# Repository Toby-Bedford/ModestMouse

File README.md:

# ModestMouse

Firmware for a dsPIC30F4011 based, maze solving, robotics platform.
<br>
<banner>ooh i can edit</banner>
</br>

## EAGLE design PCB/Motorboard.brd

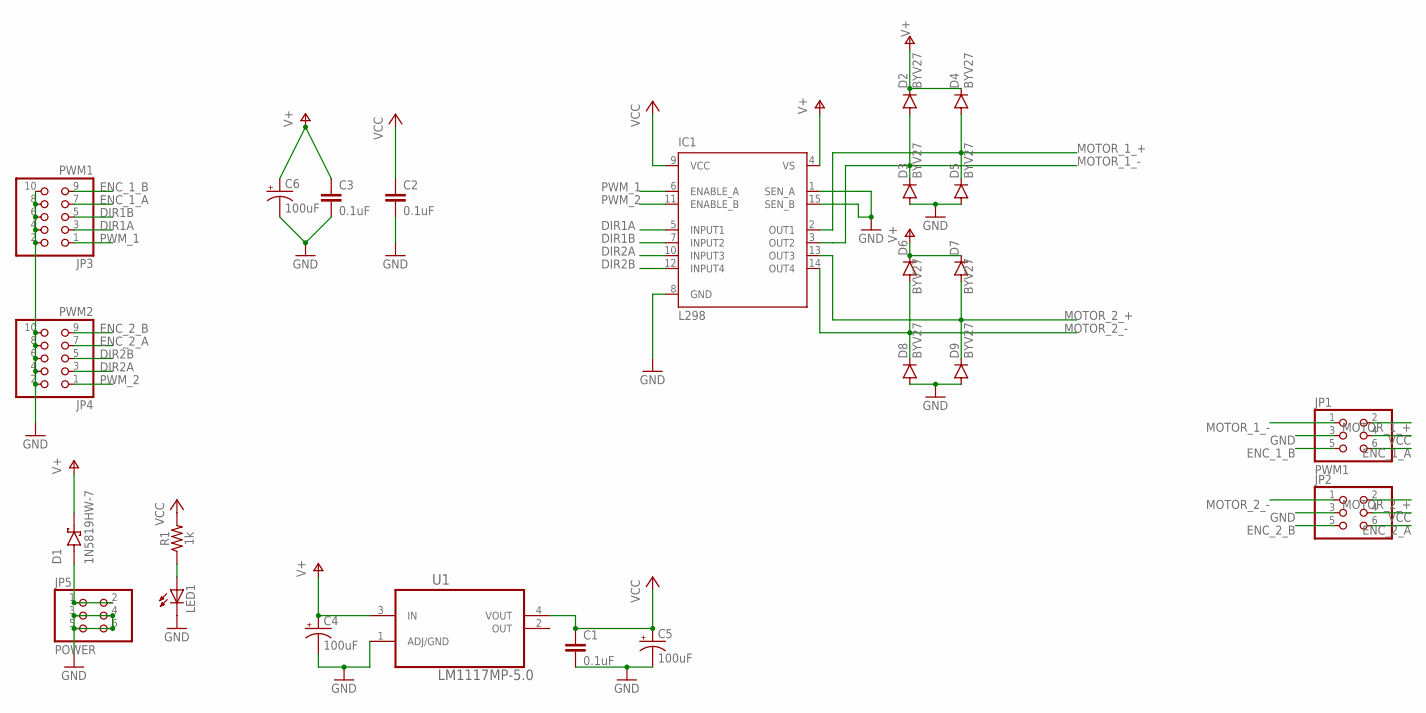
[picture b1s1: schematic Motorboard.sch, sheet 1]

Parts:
C1, C2, C3: 0.1uF; 0603
C4, C5, C6: 100uF; CPOL-RADIAL-2.5MM-6.5MM
D1: 1N5819HW-7; SOD3715X145N
D2, D3, D4, D5, D6, D7, D8, D9: BYV27; SOD57-10
IC1: L298; MULTIWATT-15
JP1: PWM1; 2X03
JP2: PINHD-2X3; 2X03
JP3: PWM1; 2X05
JP4: PWM2; 2X05
JP5: POWER; 2X03
LED1: LED3MM
R1: 1k; 0603
U1: LM1117MP-5.0; SOT230P696X180-4N

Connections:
+5V: C1.1, C2.1, C5.1 (+), IC1.9 (VCC), R1.2, U1.4 (VOUT)
DIR1A: IC1.5 (INPUT1), JP3.3
DIR1B: IC1.7 (INPUT2), JP3.5
DIR2A: IC1.10 (INPUT3), JP4.3
DIR2B: IC1.12 (INPUT4), JP4.5
ENC_1_A: JP1.6, JP3.7
ENC_1_B: JP1.5, JP3.9
ENC_2_A: JP2.6, JP4.7
ENC_2_B: JP2.5, JP4.9
GND: C1.2, C2.2, C3.2, C4.2 (-), C5.2 (-), C6.2 (-), D3.A, D5.A, D8.A, D9.A, IC1.1 (SEN_A), IC1.8 (GND), IC1.15 (SEN_B), JP1.3, JP2.3, JP3.2, JP3.4, JP3.6, JP3.8, JP3.10, JP4.2, JP4.4, JP4.6, JP4.8, JP4.10, JP5.3, JP5.4, JP5.5, JP5.6, LED1.K (C), U1.1 (ADJ/GND)
MOTOR_1_+: D4.A, D5.C, IC1.2 (OUT1), JP1.2
MOTOR_1_-: D2.A, D3.C, IC1.3 (OUT2), JP1.1
MOTOR_2_+: D7.A, D9.C, IC1.13 (OUT3), JP2.2
MOTOR_2_-: D6.A, D8.C, IC1.14 (OUT4), JP2.1
unnamed: LED1.A, R1.1
unnamed: D1.A, JP5.1, JP5.2
PWM_1: IC1.6 (ENABLE_A), JP3.1
PWM_2: IC1.11 (ENABLE_B), JP4.1
V+: C3.1, C4.1 (+), C6.1 (+), D1.C (K), D2.C, D4.C, D6.C, D7.C, IC1.4 (VS), U1.3 (IN)
VCC: JP1.4, JP2.4

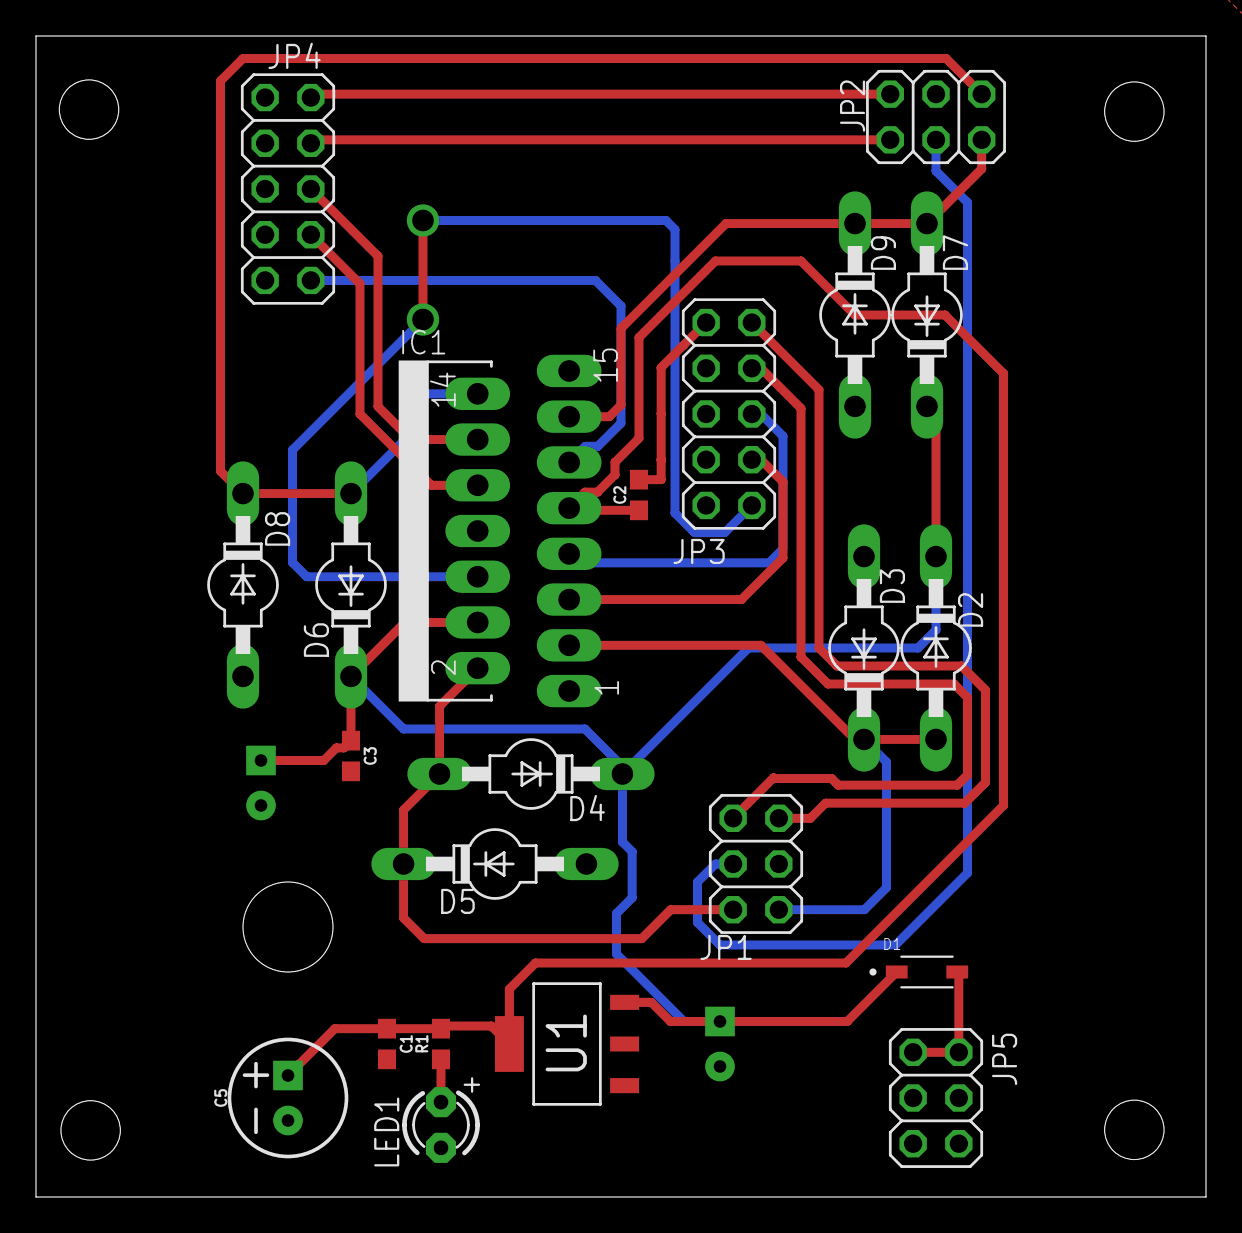
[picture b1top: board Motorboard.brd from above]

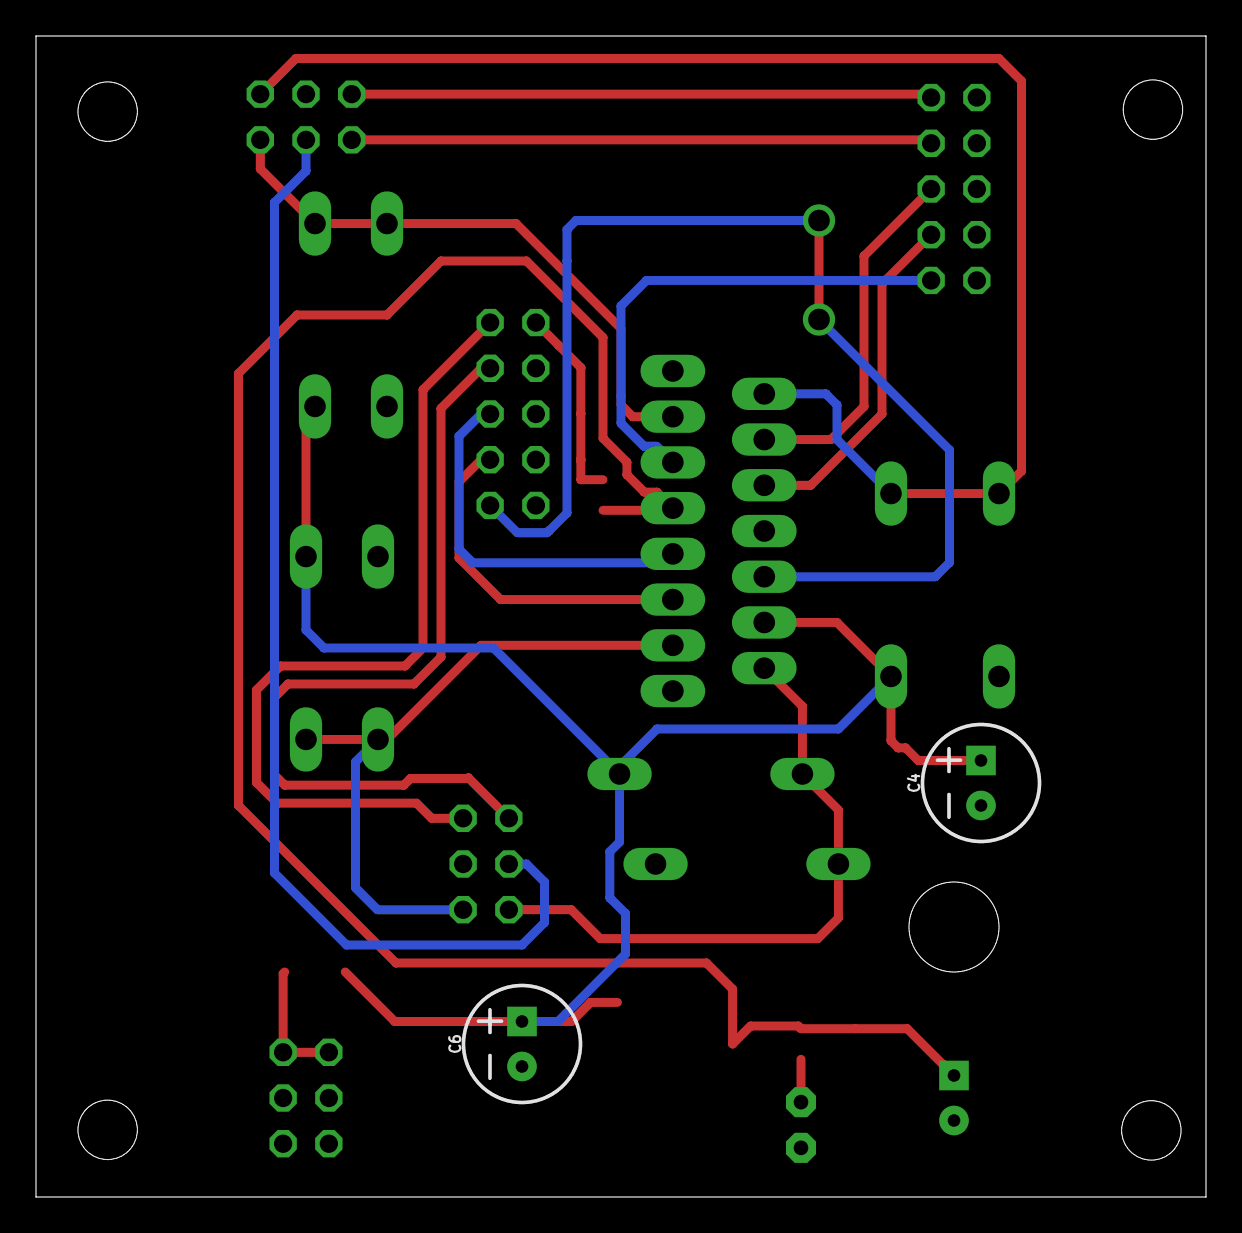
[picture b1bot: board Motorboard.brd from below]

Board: 2 copper layers, 65.0 x 64.5 mm, 24 parts (2 on the bottom side), 20 nets.

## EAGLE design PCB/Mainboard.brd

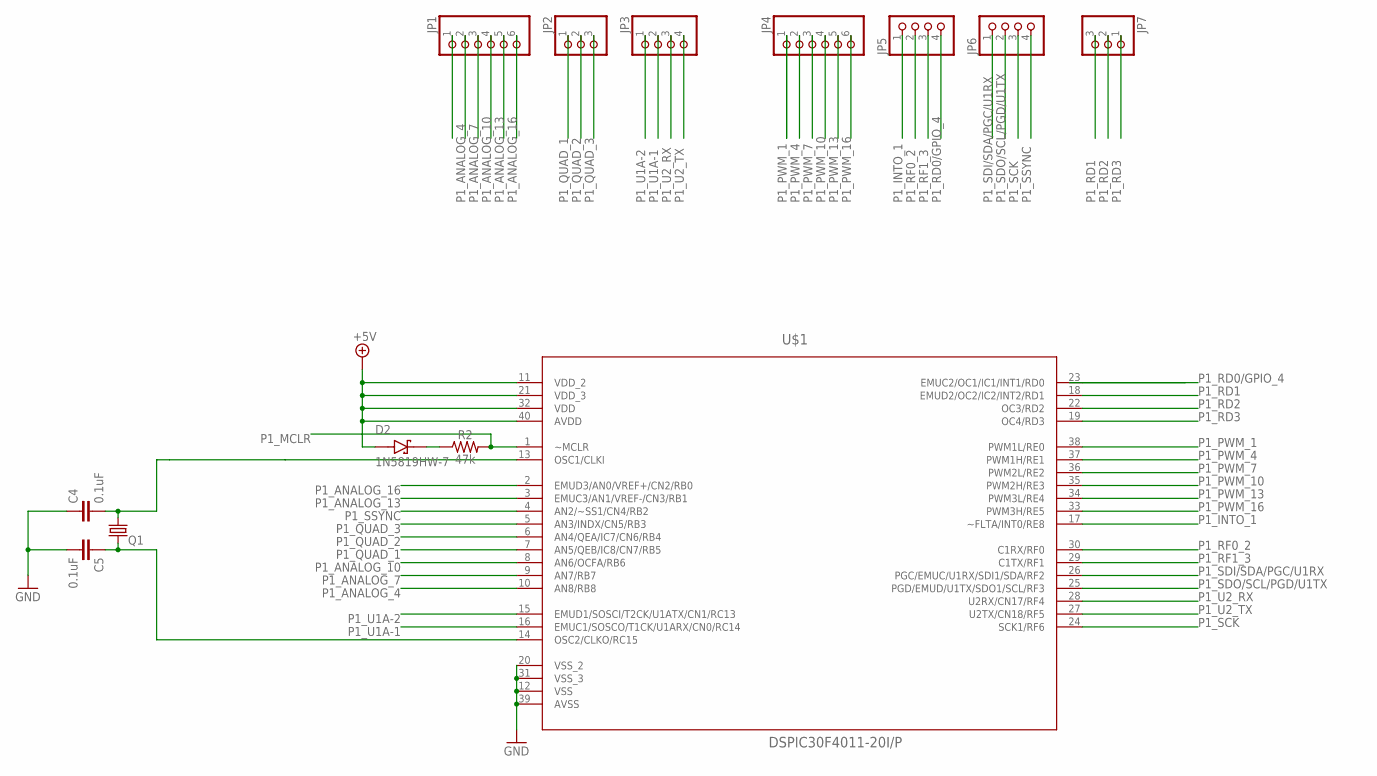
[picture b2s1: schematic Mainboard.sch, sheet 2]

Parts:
C4, C5: 0.1uF; 0603
D2: 1N5819HW-7; SOD3715X145N
JP1, JP4: PINHD-1X6; 1X06
JP2, JP7: PINHD-1X3; 1X03
JP3, JP5, JP6: PINHD-1X4; 1X04
Q1: CRYSTALHC49UP; HC49UP
R2: 47k; 0603
U$1: DSPIC30F4011-20I/P; DIP254P1524X635-40

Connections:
+5V: D2.A, U$1.11 (VDD_2), U$1.21 (VDD_3), U$1.32 (VDD), U$1.40 (AVDD); also elsewhere on the board
GND: C4.1, C5.2, U$1.12 (VSS), U$1.20 (VSS_2), U$1.31 (VSS_3), U$1.39 (AVSS); also elsewhere on the board
unnamed: C4.2, Q1.2, U$1.13 (OSC1/CLKI)
unnamed: D2.C (K), R2.1
unnamed: C5.1, Q1.1, U$1.14 (OSC2/CLKO/RC15)
P1_ANALOG_4: JP1.2, U$1.10 (AN8/RB8)
P1_ANALOG_7: JP1.3, U$1.9 (AN7/RB7)
P1_ANALOG_10: JP1.4, U$1.8 (AN6/OCFA/RB6)
P1_ANALOG_13: JP1.5, U$1.3 (EMUC3/AN1/VREF-/CN3/RB1)
P1_ANALOG_16: JP1.6, U$1.2 (EMUD3/AN0/VREF+/CN2/RB0)
P1_INTO_1: JP5.1, U$1.17 (~FLTA/INT0/RE8)
P1_MCLR: R2.2, U$1.1 (~MCLR)
P1_PWM_1: JP4.1, U$1.38 (PWM1L/RE0)
P1_PWM_4: JP4.2, U$1.37 (PWM1H/RE1)
P1_PWM_7: JP4.3, U$1.36 (PWM2L/RE2)
P1_PWM_10: JP4.4, U$1.35 (PWM2H/RE3)
P1_PWM_13: JP4.5, U$1.34 (PWM3L/RE4)
P1_PWM_16: JP4.6, U$1.33 (PWM3H/RE5)
P1_QUAD_1: JP2.1, U$1.7 (AN5/QEB/IC8/CN7/RB5)
P1_QUAD_2: JP2.2, U$1.6 (AN4/QEA/IC7/CN6/RB4)
P1_QUAD_3: JP2.3, U$1.5 (AN3/INDX/CN5/RB3)
P1_RD0/GPIO_4: JP5.4, U$1.23 (EMUC2/OC1/IC1/INT1/RD0)
P1_RD1: JP7.3, U$1.18 (EMUD2/OC2/IC2/INT2/RD1)
P1_RD2: JP7.2, U$1.22 (OC3/RD2)
P1_RD3: JP7.1, U$1.19 (OC4/RD3)
P1_RF0_2: JP5.2, U$1.30 (C1RX/RF0)
P1_RF1_3: JP5.3, U$1.29 (C1TX/RF1)
P1_SCK: JP6.3, U$1.24 (SCK1/RF6)
P1_SDI/SDA/PGC/U1RX: JP6.1, U$1.26 (PGC/EMUC/U1RX/SDI1/SDA/RF2)
P1_SDO/SCL/PGD/U1TX: JP6.2, U$1.25 (PGD/EMUD/U1TX/SDO1/SCL/RF3)
P1_SSYNC: JP6.4, U$1.4 (AN2/~SS1/CN4/RB2)
P1_U1A-1: JP3.2, U$1.16 (EMUC1/SOSCO/T1CK/U1ARX/CN0/RC14)
P1_U1A-2: JP3.1, U$1.15 (EMUD1/SOSCI/T2CK/U1ATX/CN1/RC13)
P1_U2_RX: JP3.3, U$1.28 (U2RX/CN17/RF4)
P1_U2_TX: JP3.4, U$1.27 (U2TX/CN18/RF5)

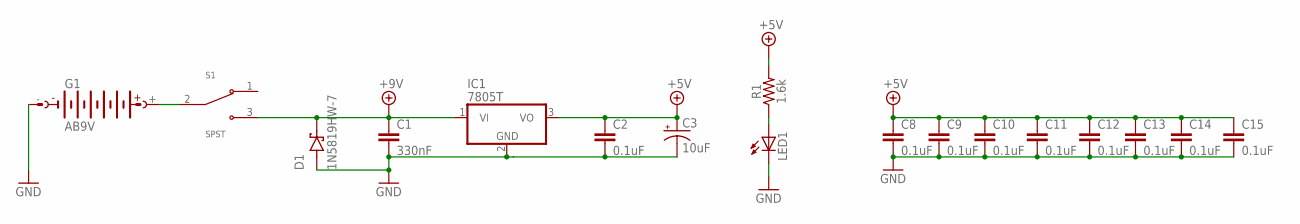
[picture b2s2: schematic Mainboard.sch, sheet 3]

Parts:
C1: 330nF; 0603
C2, C8, C9, C10, C11, C12, C13, C14, C15: 0.1uF; 0603
C3: 10uF; CPOL-RADIAL-2.5MM-5MM
D1: 1N5819HW-7; SOD3715X145N
G1: AB9V
IC1: 7805T; TO220H
LED1: LED3MM
R1: 1.6k; 0603
S1: SPST

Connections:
+5V: C2.1, C3.1 (+), C8.1, C9.1, C10.1, C11.1, C12.1, C13.1, C14.1, C15.1, IC1.3 (VO), R1.2; also elsewhere on the board
+9V: C1.1, D1.C (K), IC1.1 (VI), S1.3
GND: C1.2, C2.2, C3.2 (-), C8.2, C9.2, C10.2, C11.2, C12.2, C13.2, C14.2, C15.2, D1.A, G1.-, IC1.2 (GND), LED1.K (C); also elsewhere on the board
unnamed: G1.+, S1.2
unnamed: LED1.A, R1.1

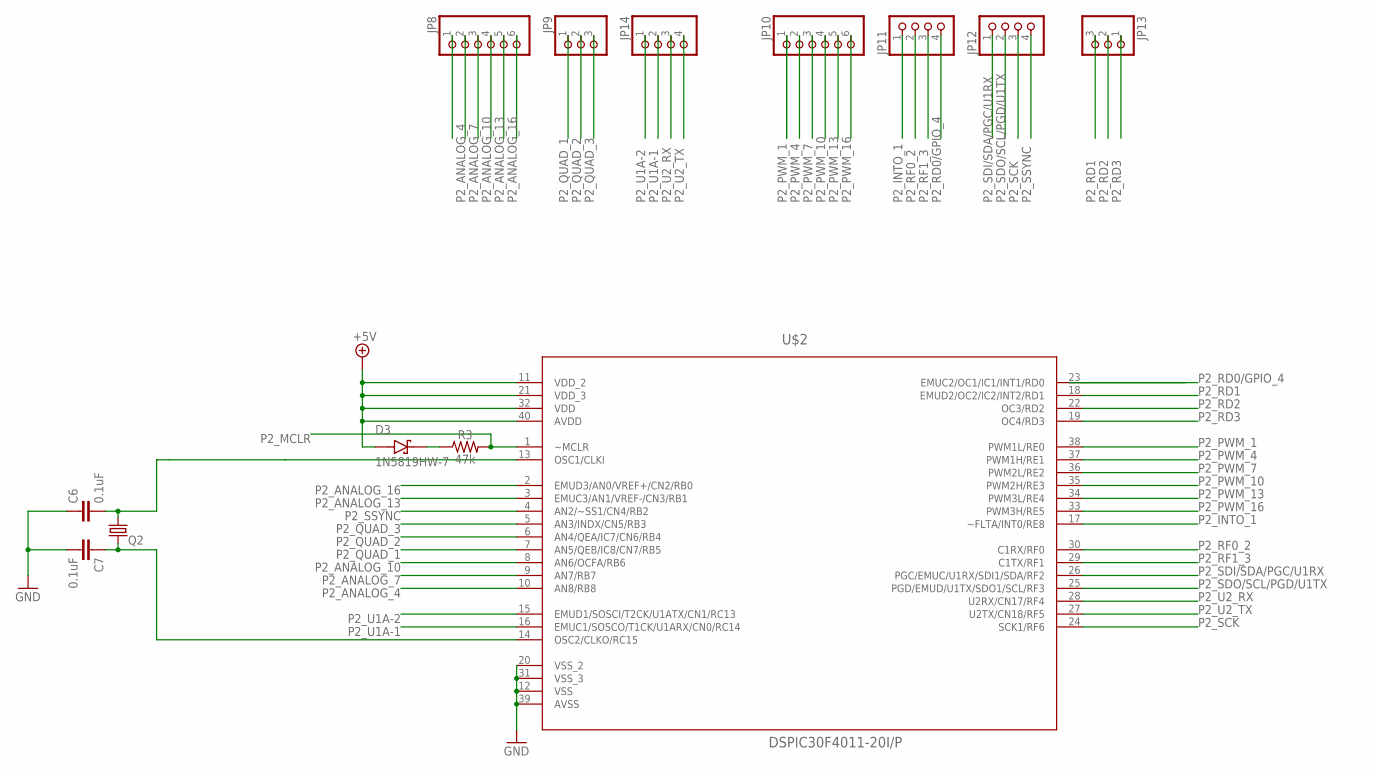
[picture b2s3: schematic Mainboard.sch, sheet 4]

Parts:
C6, C7: 0.1uF; 0603
D3: 1N5819HW-7; SOD3715X145N
JP8, JP10: PINHD-1X6; 1X06
JP9, JP13: PINHD-1X3; 1X03
JP11, JP12, JP14: PINHD-1X4; 1X04
Q2: CRYSTALHC49UP; HC49UP
R3: 47k; 0603
U$2: DSPIC30F4011-20I/P; DIP254P1524X635-40

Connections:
+5V: D3.A, U$2.11 (VDD_2), U$2.21 (VDD_3), U$2.32 (VDD), U$2.40 (AVDD); also elsewhere on the board
GND: C6.1, C7.2, U$2.12 (VSS), U$2.20 (VSS_2), U$2.31 (VSS_3), U$2.39 (AVSS); also elsewhere on the board
unnamed: D3.C (K), R3.1
unnamed: C6.2, Q2.2, U$2.13 (OSC1/CLKI)
unnamed: C7.1, Q2.1, U$2.14 (OSC2/CLKO/RC15)
P2_ANALOG_4: JP8.2, U$2.10 (AN8/RB8)
P2_ANALOG_7: JP8.3, U$2.9 (AN7/RB7)
P2_ANALOG_10: JP8.4, U$2.8 (AN6/OCFA/RB6)
P2_ANALOG_13: JP8.5, U$2.3 (EMUC3/AN1/VREF-/CN3/RB1)
P2_ANALOG_16: JP8.6, U$2.2 (EMUD3/AN0/VREF+/CN2/RB0)
P2_INTO_1: JP11.1, U$2.17 (~FLTA/INT0/RE8)
P2_MCLR: R3.2, U$2.1 (~MCLR)
P2_PWM_1: JP10.1, U$2.38 (PWM1L/RE0)
P2_PWM_4: JP10.2, U$2.37 (PWM1H/RE1)
P2_PWM_7: JP10.3, U$2.36 (PWM2L/RE2)
P2_PWM_10: JP10.4, U$2.35 (PWM2H/RE3)
P2_PWM_13: JP10.5, U$2.34 (PWM3L/RE4)
P2_PWM_16: JP10.6, U$2.33 (PWM3H/RE5)
P2_QUAD_1: JP9.1, U$2.7 (AN5/QEB/IC8/CN7/RB5)
P2_QUAD_2: JP9.2, U$2.6 (AN4/QEA/IC7/CN6/RB4)
P2_QUAD_3: JP9.3, U$2.5 (AN3/INDX/CN5/RB3)
P2_RD0/GPIO_4: JP11.4, U$2.23 (EMUC2/OC1/IC1/INT1/RD0)
P2_RD1: JP13.3, U$2.18 (EMUD2/OC2/IC2/INT2/RD1)
P2_RD2: JP13.2, U$2.22 (OC3/RD2)
P2_RD3: JP13.1, U$2.19 (OC4/RD3)
P2_RF0_2: JP11.2, U$2.30 (C1RX/RF0)
P2_RF1_3: JP11.3, U$2.29 (C1TX/RF1)
P2_SCK: JP12.3, U$2.24 (SCK1/RF6)
P2_SDI/SDA/PGC/U1RX: JP12.1, U$2.26 (PGC/EMUC/U1RX/SDI1/SDA/RF2)
P2_SDO/SCL/PGD/U1TX: JP12.2, U$2.25 (PGD/EMUD/U1TX/SDO1/SCL/RF3)
P2_SSYNC: JP12.4, U$2.4 (AN2/~SS1/CN4/RB2)
P2_U1A-1: JP14.2, U$2.16 (EMUC1/SOSCO/T1CK/U1ARX/CN0/RC14)
P2_U1A-2: JP14.1, U$2.15 (EMUD1/SOSCI/T2CK/U1ATX/CN1/RC13)
P2_U2_RX: JP14.3, U$2.28 (U2RX/CN17/RF4)
P2_U2_TX: JP14.4, U$2.27 (U2TX/CN18/RF5)

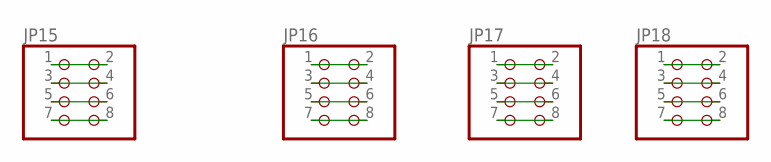
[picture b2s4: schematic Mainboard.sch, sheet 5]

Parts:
JP15, JP16, JP17, JP18: PINHD-2X4; 2X04

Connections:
unnamed: JP15.1, JP15.2
unnamed: JP15.3, JP15.4
unnamed: JP15.5, JP15.6
unnamed: JP15.7, JP15.8
unnamed: JP16.1, JP16.2
unnamed: JP16.3, JP16.4
unnamed: JP16.5, JP16.6
unnamed: JP16.7, JP16.8
unnamed: JP17.1, JP17.2
unnamed: JP17.3, JP17.4
unnamed: JP17.5, JP17.6
unnamed: JP17.7, JP17.8
unnamed: JP18.1, JP18.2
unnamed: JP18.3, JP18.4
unnamed: JP18.5, JP18.6
unnamed: JP18.7, JP18.8

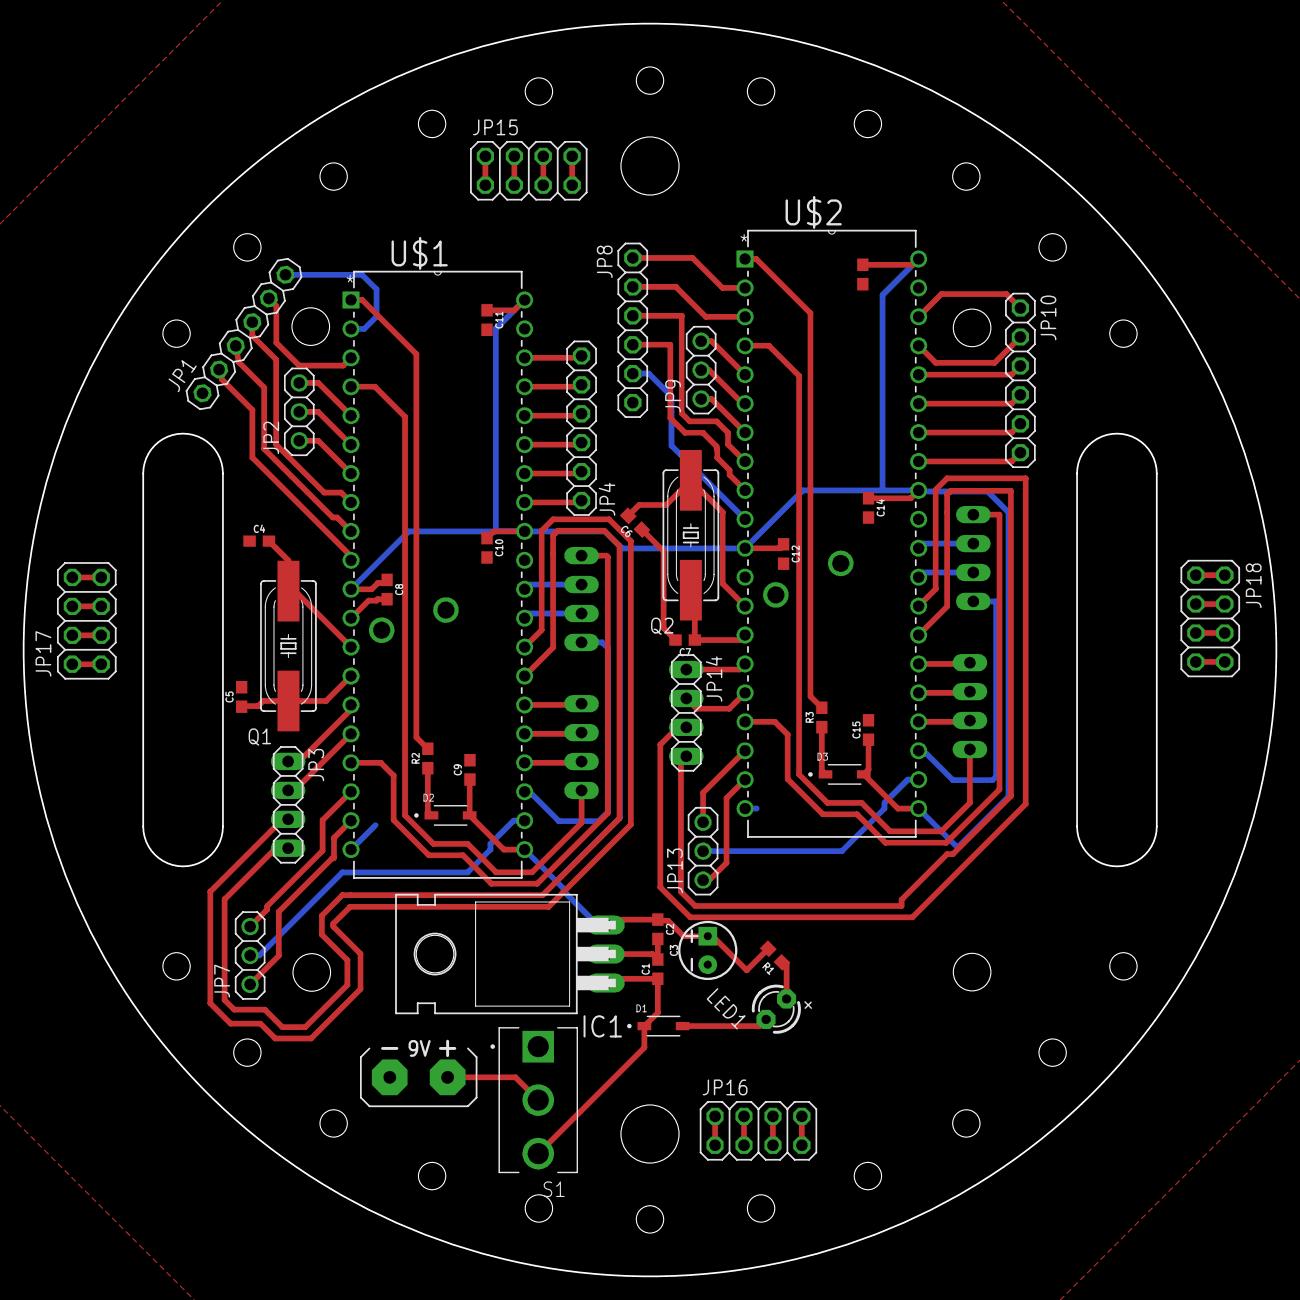
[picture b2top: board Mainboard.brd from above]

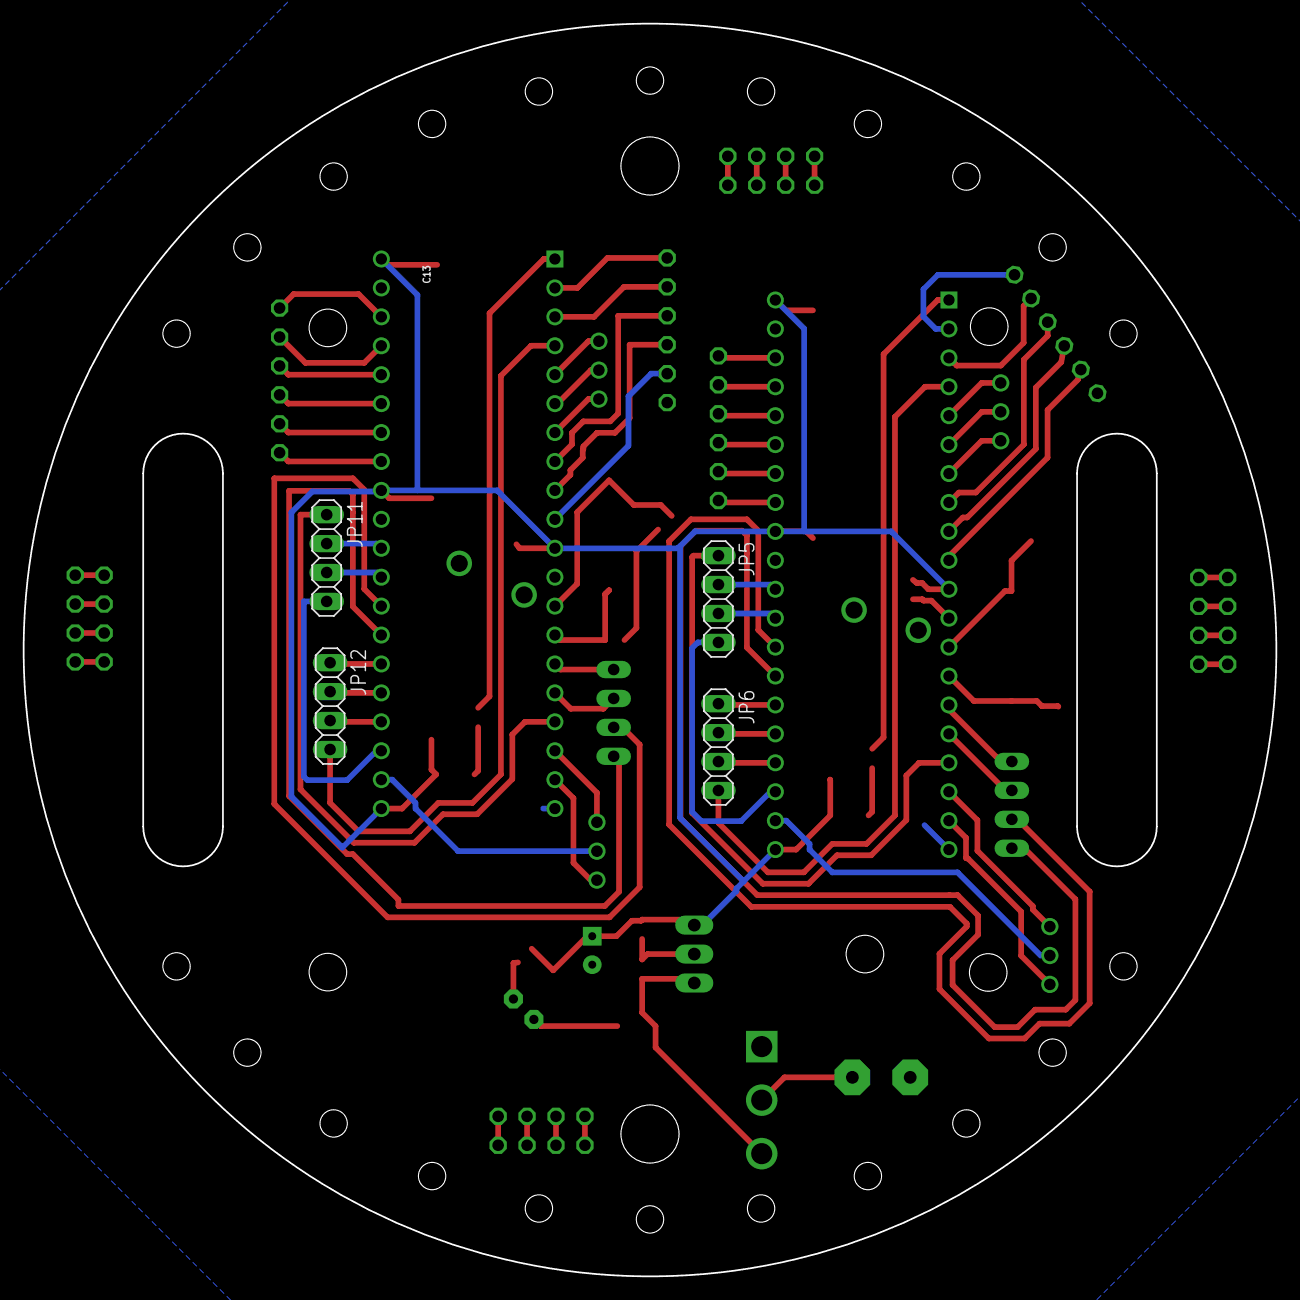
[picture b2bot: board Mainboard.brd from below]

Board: 2 copper layers, 110.0 x 110.0 mm, 47 parts (4 on the bottom side), 87 nets.

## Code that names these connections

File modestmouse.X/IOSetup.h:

/* 
 * File:   IOSetup.h
 * Author: harry
 *
 * Created on 11 January 2022, 20:32
 */

#ifndef IOSETUP_H
#define	IOSETUP_H

#include "p30F4011.h"


#ifdef	__cplusplus
extern "C" {
#endif

//Defining S3
#define S3PORT PORTDbits.RD2
#define S3TRIS TRISDbits.TRISD2
#define S3LAT LATDbits.LATD2
    
//Defining LED2
#define LED2PORT PORTDbits.RD1
#define LED2TRIS TRISDbits.TRISD1
#define LED2LAT LATDbits.LATD1
    
//Defining LED3
#define LED3PORT PORTDbits.RD3
#define LED3TRIS TRISDbits.TRISD3
#define LED3LAT LATDbits.LATD3
    
//Defining LED4
#define LED4PORT PORTEbits.RE0
#define LED4TRIS TRISEbits.TRISE0
#define LED4LAT LATEbits.LATE0
    
// 23/03/2022
// Switched motors pins to from RB7 --> RB5 & RB8 --> RB6
#define PIN37PORT PORTBbits.RB5
#define PIN37TRIS TRISBbits.TRISB5
#define PIN37LAT LATBbits.LATB5
    
#define PIN36PORT PORTBbits.RB6
#define PIN36TRIS TRISBbits.TRISB6
#define PIN36LAT LATBbits.LATB6

// Added setup pins for ultrasonic sensor.
#define echoPin PORTBbits.RB7
#define ECHO_tris TRISBbits.TRISB7
    
#define TRIG_tris TRISBbits.TRISB8
#define trigPin LATBbits.LATB8
 

void GPIOSetup(void);
    

#ifdef	__cplusplus
}
#endif

#endif	/* IOSETUP_H */

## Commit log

2022-02-15 Adding MPLAB X project with required source and header files.
2022-02-15 Adding main.c and p30F4011.h
2022-02-16 Adding setup source and header files for IO, PWM, QEI, Timer1 and UART.
2022-02-23 added test message
2022-03-11 Adding ADC setup header and source files
2022-03-11 General purpose uart functions
2022-03-11 UART c files
2022-03-23 Sensor code with 10us pulse and basic reading over UART.
2022-03-24 Sensors
    Added functionality to show distance in cm from ultrasonic sensor over UART2.
2022-03-30 Create CAD Models

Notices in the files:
parts and their libraries:
SparkFun-Capacitors: Licensing: Creative Commons ShareAlike 4.0 International - https://creativecommons.org/licenses/by-sa/4.0
